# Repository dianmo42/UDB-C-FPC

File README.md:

# UDB-C-FPC
Modified based on [Unified Daughterboard](https://unified-daughterboard.github.io/#/). The connector has been replace with the FPC connector.

### Attention!
The feasibility of this project is not guaranteed. Please conduct sample testing before proceeding to formal production.

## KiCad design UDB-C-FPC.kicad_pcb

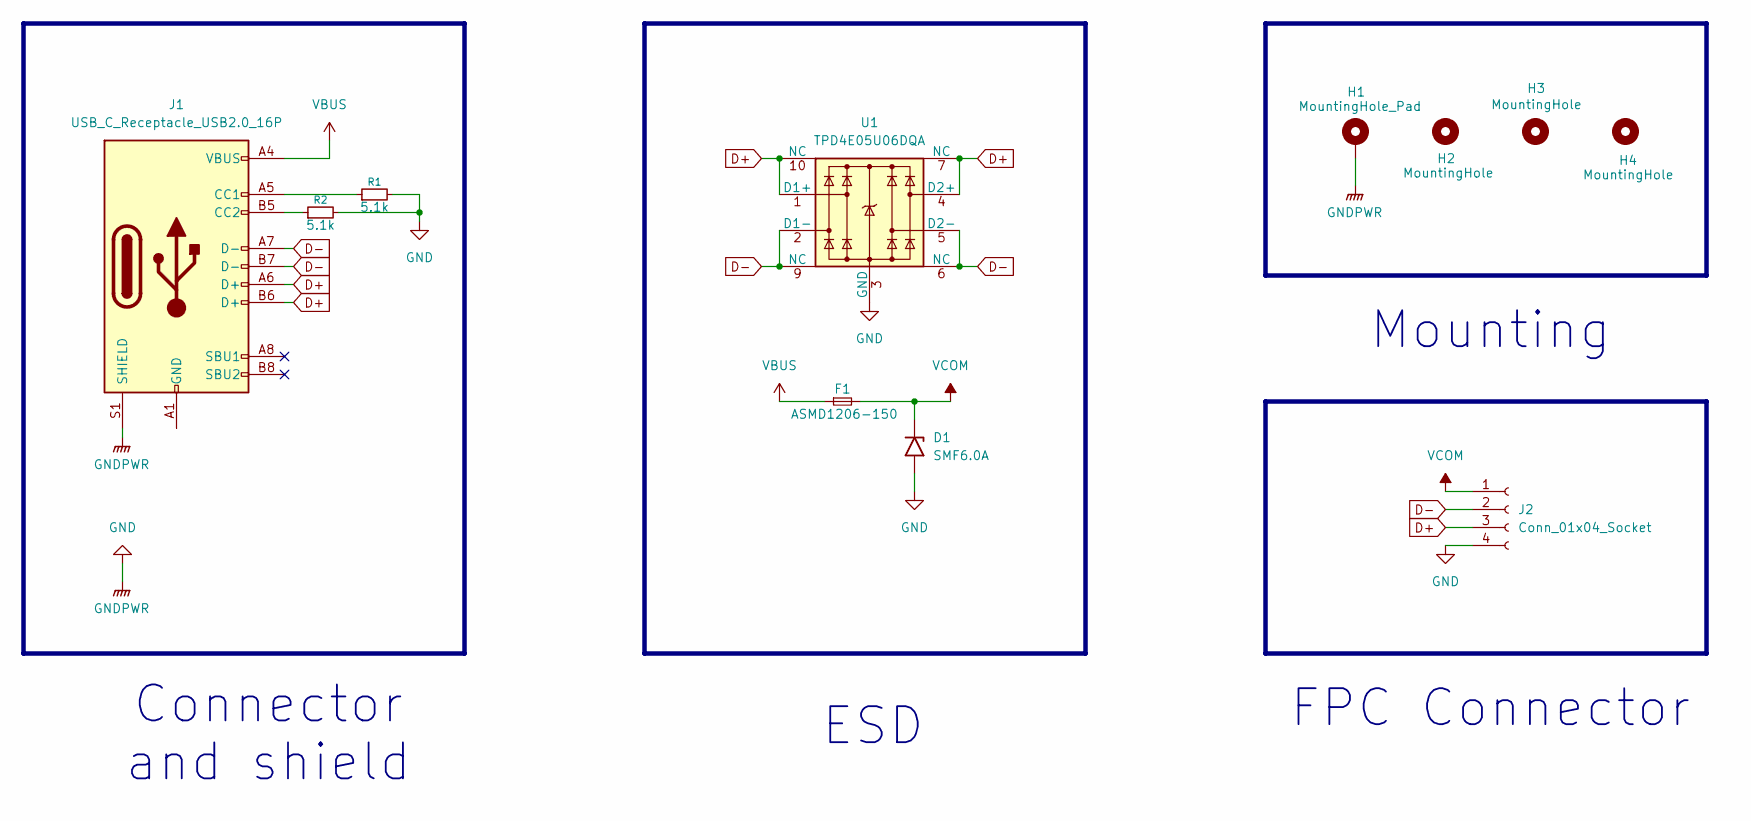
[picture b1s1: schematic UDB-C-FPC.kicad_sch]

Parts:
D1: SMF6.0A; D_SOD-123
F1: ASMD1206-150; Fuse_1206_3216Metric
H1: MountingHole_Pad; MountingHole_2.2mm_M2_DIN965_Pad
H2, H3, H4: MountingHole; MountingHole_2.2mm_M2
J1: USB_C_Receptacle_USB2.0_16P; USB_C_Receptacle_HRO_TYPE-C-31-M-12
J2: Conn_01x04_Socket; Amphenol_F32R-1A7x1-11004_1x04-1MP_P0.5mm_Horizontal
R1, R2: 5.1k; R_0402_1005Metric
U1: TPD4E05U06DQA; USON-10_2.5x1.0mm_P0.5mm

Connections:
D+: J1.A6 (D+), J1.B6 (D+), J2.3, U1.1 (D1+), U1.4 (D2+), U1.7 (NC), U1.10 (NC)
D-: J1.A7 (D-), J1.B7 (D-), J2.2, U1.2 (D1-), U1.5 (D2-), U1.6 (NC), U1.9 (NC)
GND: D1.2 (A2), H1.1, J1.S1 (SHIELD), J2.4, R1.2, R2.2, U1.3 (GND), U1.8 (GND)
unnamed: J1.A5 (CC1), R1.1
unnamed: J1.B5 (CC2), R2.1
unnamed: J1.A1 (GND), J1.A12 (GND), J1.B1 (GND), J1.B12 (GND)
VBUS: F1.1, J1.A4 (VBUS), J1.A9 (VBUS), J1.B4 (VBUS), J1.B9 (VBUS)
VCOM: D1.1 (A1), F1.2, J2.1

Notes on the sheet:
FPC Connector
Connector and shield
Mounting
ESD

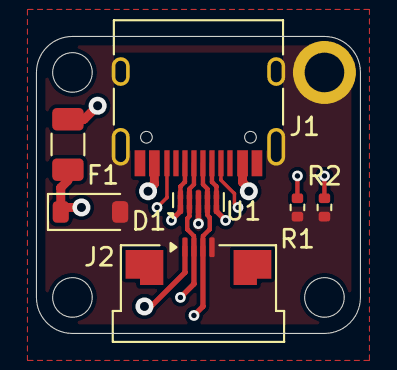
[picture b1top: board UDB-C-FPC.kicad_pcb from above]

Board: 4 copper layers, 18.0 x 16.5 mm, 11 parts (0 on the bottom side), 8 nets.

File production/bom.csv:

Designator,Footprint,Quantity,Value,LCSC Part #
D1,D_SOD-123,1,SMF6.0A,
F1,1206,1,ASMD1206-150,
J1,USB_C_Receptacle_HRO_TYPE-C-31-M-12,1,USB_C_Receptacle_USB2.0_16P,
J2,Amphenol_F32R-1A7x1-11004_1x04-1MP_P0.5mm_Horizontal,1,Conn_01x04_Socket,
"R1, R2",0402,2,5.1k,
U1,USON-10_2.5x1.0mm_P0.5mm,1,TPD4E05U06DQA,

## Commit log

2025-09-03 UDB-C5 with FPC connector
